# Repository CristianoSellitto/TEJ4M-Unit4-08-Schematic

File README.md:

# TEJ4M-Unit4-08-Schematic

Contains the electronic schematic & PCB for Unit4-08

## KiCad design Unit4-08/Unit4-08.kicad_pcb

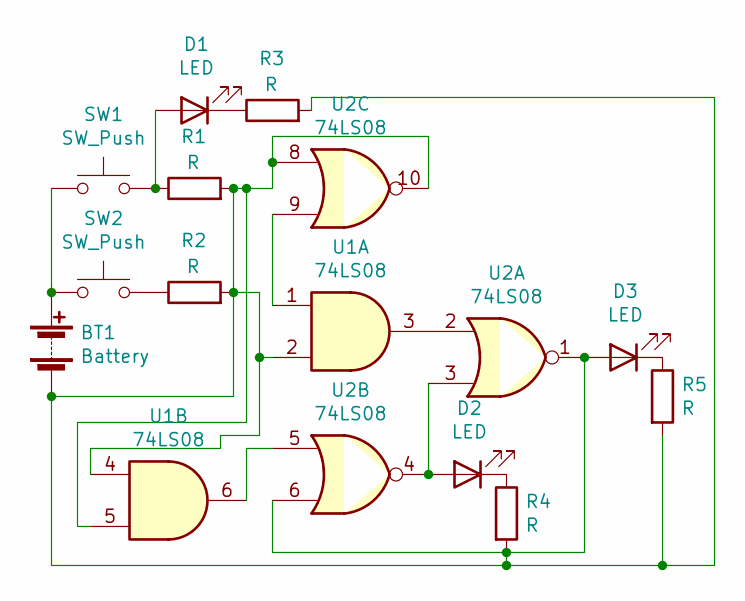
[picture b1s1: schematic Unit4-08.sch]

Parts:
BT1: Battery; BatteryHolder_Bulgin_BX0036_1xC
D1, D2, D3: LED; LED-L1T2_LUMILEDS
R1, R2, R3, R4, R5: R; R_0201_0603Metric
SW1, SW2: SW_Push; SW_Push_1P1T_NO_6x6mm_H9.5mm
U1, U2: 74LS08; SOIC-14_3.9x8.7mm_P1.27mm

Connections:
unnamed: BT1.1 (+), SW1.1, SW2.1
unnamed: BT1.2 (-), D3.2 (A), R1.2, R2.2, R3.2, R4.2, R5.2, U1.2, U1.4, U1.5, U2.1, U2.6, U2.8, U2.10
unnamed: D1.1 (K), R3.1
unnamed: D1.2 (A), R1.1, SW1.2
unnamed: D2.1 (K), R4.1
unnamed: D2.2 (A), U2.3, U2.4
unnamed: D3.1 (K), R5.1
unnamed: R2.1, SW2.2
unnamed: U1.1, U2.9
unnamed: U1.3, U2.2
unnamed: U1.6, U2.5

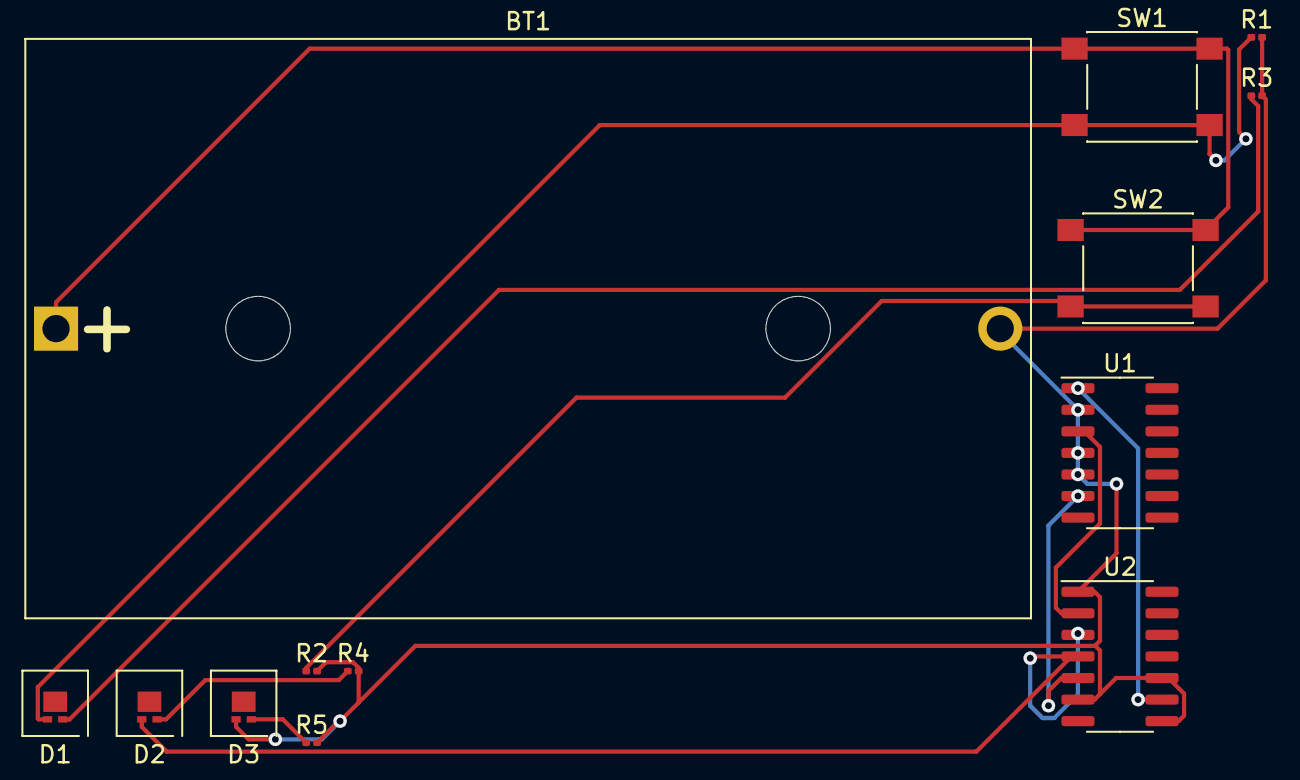
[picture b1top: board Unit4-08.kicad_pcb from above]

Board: 2 copper layers, 13 parts (0 on the bottom side), 11 nets.

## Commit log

2023-10-30 SSH Import
2023-10-30 Changed README wording
2023-10-31 Updated PCB
